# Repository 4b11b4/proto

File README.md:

# proto-pcb
free prototyping boards

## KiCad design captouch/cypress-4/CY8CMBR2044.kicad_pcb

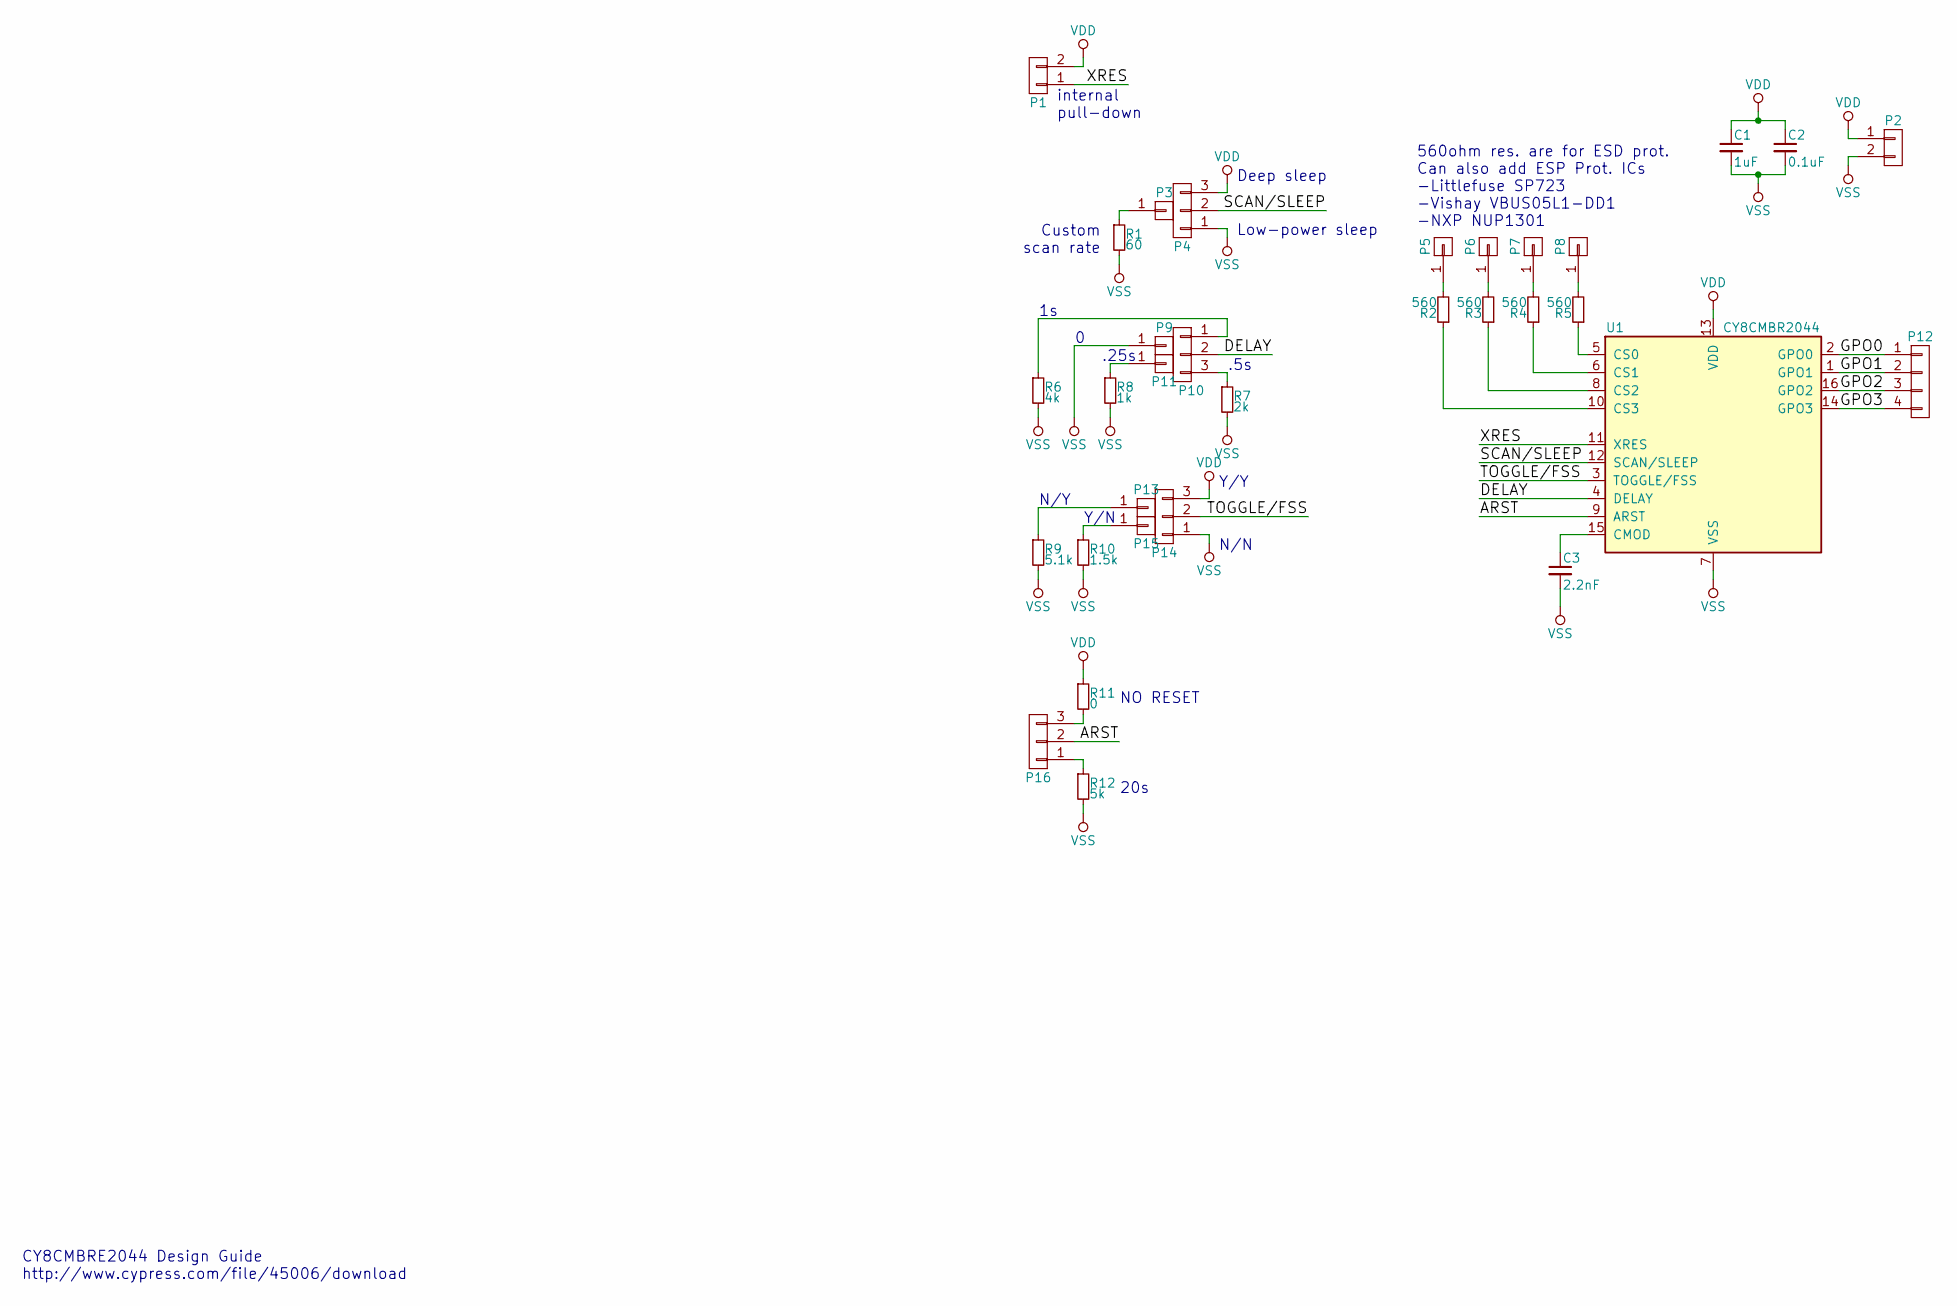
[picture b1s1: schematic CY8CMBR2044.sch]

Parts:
C1: 1uF; C_1206_HandSoldering
C2: 0.1uF; C_1206_HandSoldering
C3: 2.2nF; C_0603_HandSoldering; Mfr Part # GRM1885C1H222JA01D
P1, P2: CONN_01X02; Pin_Header_Straight_1x02
P3, P5, P6, P7, P8, P9, P11, P13, P15: CONN_01X01; Pin_Header_Straight_1x01
P4, P10, P14, P16: CONN_01X03; Pin_Header_Straight_1x03
P12: CONN_01X04; Pin_Header_Straight_1x04
R1: 60; R_1206_HandSoldering
R2, R3, R4, R5: 560; R_1206_HandSoldering
R6: 4k; R_1206_HandSoldering
R7: 2k; R_1206_HandSoldering
R8: 1k; R_1206_HandSoldering
R9: 5.1k; R_1206_HandSoldering
R10: 1.5k; R_1206_HandSoldering
R11: 0; R_1206_HandSoldering
R12: 5k; R_1206_HandSoldering
U1: CY8CMBR2044; QFN-16_3x3mm_Pitch0.5mm; Mfr Part # CY8CMBR2044

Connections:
/ARST: P16.2, U1.9 (ARST)
/DELAY: P10.2, U1.4 (DELAY)
/GPO0: P12.1, U1.2 (GPO0)
/GPO1: P12.2, U1.1 (GPO1)
/GPO2: P12.3, U1.16 (GPO2)
/GPO3: P12.4, U1.14 (GPO3)
/SCAN/SLEEP: P4.2, U1.12 (SCAN/SLEEP)
/TOGGLE/FSS: P14.2, U1.3 (TOGGLE/FSS)
/XRES: P1.1, U1.11 (XRES)
unnamed: C3.1, U1.15 (CMOD)
unnamed: P3.1, R1.1
unnamed: P5.1, R2.2
unnamed: P6.1, R3.2
unnamed: P7.1, R4.2
unnamed: P8.1, R5.2
unnamed: P10.1, R6.1
unnamed: P10.3, R7.1
unnamed: P11.1, R8.1
unnamed: P13.1, R9.1
unnamed: P15.1, R10.1
unnamed: P16.1, R12.1
unnamed: P16.3, R11.2
unnamed: R2.1, U1.10 (CS3)
unnamed: R3.1, U1.8 (CS2)
unnamed: R4.1, U1.6 (CS1)
unnamed: R5.1, U1.5 (CS0)
VDD: C1.1, C2.1, P1.2, P2.1, P4.3, P14.3, R11.1, U1.13 (VDD)
VSS: C1.2, C2.2, C3.2, P2.2, P4.1, P9.1, P14.1, R1.2, R6.2, R7.2, R8.2, R9.2, R10.2, R12.2, U1.7 (VSS)

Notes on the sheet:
CY8CMBRE2044 Design Guide http://www.cypress.com/file/45006/download
Y/Y
N/N
N/Y
Y/N
.25s
560ohm res. are for ESD prot. Can also add ESP Prot. ICs -Littlefuse SP723 -Vishay VBUS05L1-DD1 -NXP NUP1301
Low-power sleep
Deep sleep
Custom scan rate
NO RESET
20s
.5s
internal pull-down

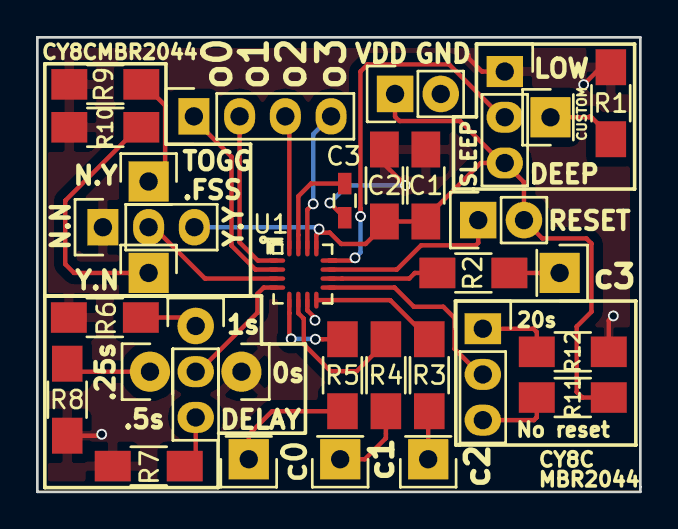
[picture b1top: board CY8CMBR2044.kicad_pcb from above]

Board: 2 copper layers, 33.5 x 25.2 mm, 32 parts (0 on the bottom side), 28 nets.

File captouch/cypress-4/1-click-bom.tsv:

References	Qty	Description	Digikey	Mouser	RS	Newark	Farnell
C1	1	1uF 0805 X5R					
C2	1	C Small 0.1uF Unpolarized capacitor 1206 HandSoldering					
C3	1	C Small 2.2nF Unpolarized capacitor 0603 HandSoldering					
P2, P1	2	CONN 01X02 Connector, single row, 01x02 Pin Header Straight 1x02					
P12	1	CONN 01X04 Connector, single row, 01x04 Pin Header Straight 1x04					
P13, P15, P9, P11, P3, P5, P6, P7, P8	9	CONN 01X01 Connector, single row, 01x01 Pin Header Straight 1x01					
P16, P14, P10, P4	4	CONN 01X03 Connector, single row, 01x03 Pin Header Straight 1x03					
R1	1	R Small 60 Resistor, small symbol 1206 HandSoldering					
R2, R3, R4, R5	4	R Small 560 Resistor, small symbol 1206 HandSoldering					
R6	1	R Small 4k Resistor, small symbol 1206 HandSoldering					
R7	1	R Small 2k Resistor, small symbol 1206 HandSoldering					
R8	1	R Small 1k Resistor, small symbol 1206 HandSoldering					
R9	1	R Small 5.1k Resistor, small symbol 1206 HandSoldering					
R10	1	R Small 1.5k Resistor, small symbol 1206 HandSoldering					
R11	1	R Small 0 Resistor, small symbol 1206 HandSoldering					
R12	1	R Small 5k Resistor, small symbol 1206 HandSoldering					
U1	1	CY8CMBR2044

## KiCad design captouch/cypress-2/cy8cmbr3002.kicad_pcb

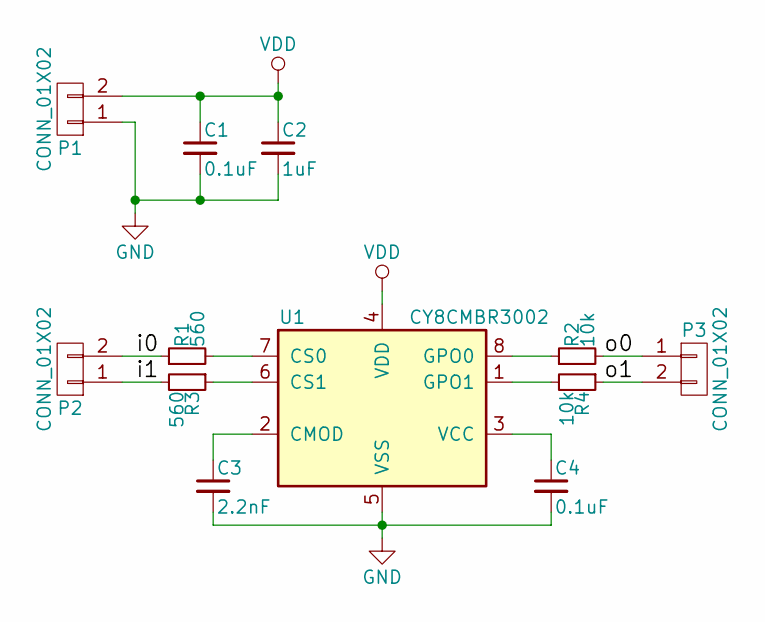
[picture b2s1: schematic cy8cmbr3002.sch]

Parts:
C1, C4: 0.1uF; C_1206_HandSoldering
C2: 1uF; C_1206_HandSoldering
C3: 2.2nF; C_1206_HandSoldering; Tolerance 5V X7R/NP0
P1, P2, P3: CONN_01X02; Pin_Header_Straight_1x02
R1, R3: 560; C_1206_HandSoldering
R2, R4: 10k; C_1206_HandSoldering
U1: CY8CMBR3002; SOIC-8-N; Mfr Part # CY8CMBR3002-SX1I

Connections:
/i0: P2.2, R1.1
/i1: P2.1, R3.2
/o0: P3.1, R2.2
/o1: P3.2, R4.1
GND: C1.2, C2.2, C3.2, C4.2, P1.1, U1.5 (VSS)
unnamed: C3.1, U1.2 (CMOD)
unnamed: C4.1, U1.3 (VCC)
unnamed: R1.2, U1.7 (CS0)
unnamed: R2.1, U1.8 (GPO0)
unnamed: R3.1, U1.6 (CS1)
unnamed: R4.2, U1.1 (GPO1)
VDD: C1.1, C2.1, P1.2, U1.4 (VDD)

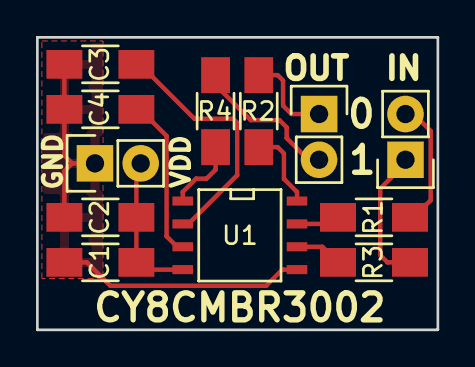
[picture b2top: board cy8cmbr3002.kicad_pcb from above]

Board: 2 copper layers, 22.3 x 16.2 mm, 12 parts (0 on the bottom side), 12 nets.

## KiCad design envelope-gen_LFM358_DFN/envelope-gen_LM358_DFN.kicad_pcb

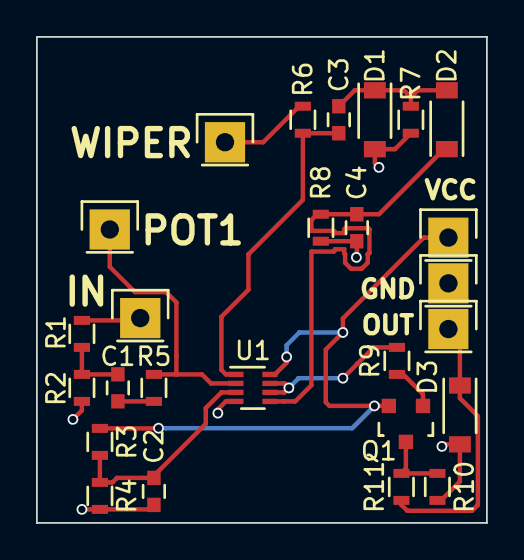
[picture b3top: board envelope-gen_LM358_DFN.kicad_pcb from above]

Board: 2 copper layers, 25.0 x 27.0 mm, 26 parts (0 on the bottom side), 15 nets.

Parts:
C1, C3: 0.22uF; C_0603
C2: 10uF; C_0603
C4: 1uF; C_0603
D1, D2: 1N4148; SOD-123
D3: 5.1V; SOD-123
P1, P2, P3, P4, P5, P6: CONN_01X01; Pin_Header_Straight_1x01
Q1: MMBT3904; SOT-23
R1, R2, R3, R4, R7, R10: 10k; R_0603
R5, R6, R9: 1k; R_0603
R8: 100k; R_0603
R11: 220; R_0603
U1: LM358; DFN-8_2x2mm_Pitch0.5mm

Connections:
/IN: P2.1, R1.1
/OUT: D3.1, P4.1, R11.2
/POT1: P5.1, R5.1, U1.2
/VCC: P3.1, Q1.2, R3.1, U1.8
/WIPER: P6.1, R6.2
GND: C2.2, C4.1, D1.2, D3.2, P1.1, R2.2, R4.2, R7.2, R8.2, R10.2, U1.4
unnamed: C1.1, R5.2
unnamed: C1.2, R1.2, R2.1
unnamed: C2.1, R3.2, R4.1, U1.3
unnamed: C3.1, D1.1, D2.2, R7.1
unnamed: C3.2, R6.1, U1.1
unnamed: C4.2, D2.1, R8.1, U1.5
unnamed: Q1.1, R9.1
unnamed: Q1.3, R10.1, R11.1
unnamed: R9.2, U1.6, U1.7

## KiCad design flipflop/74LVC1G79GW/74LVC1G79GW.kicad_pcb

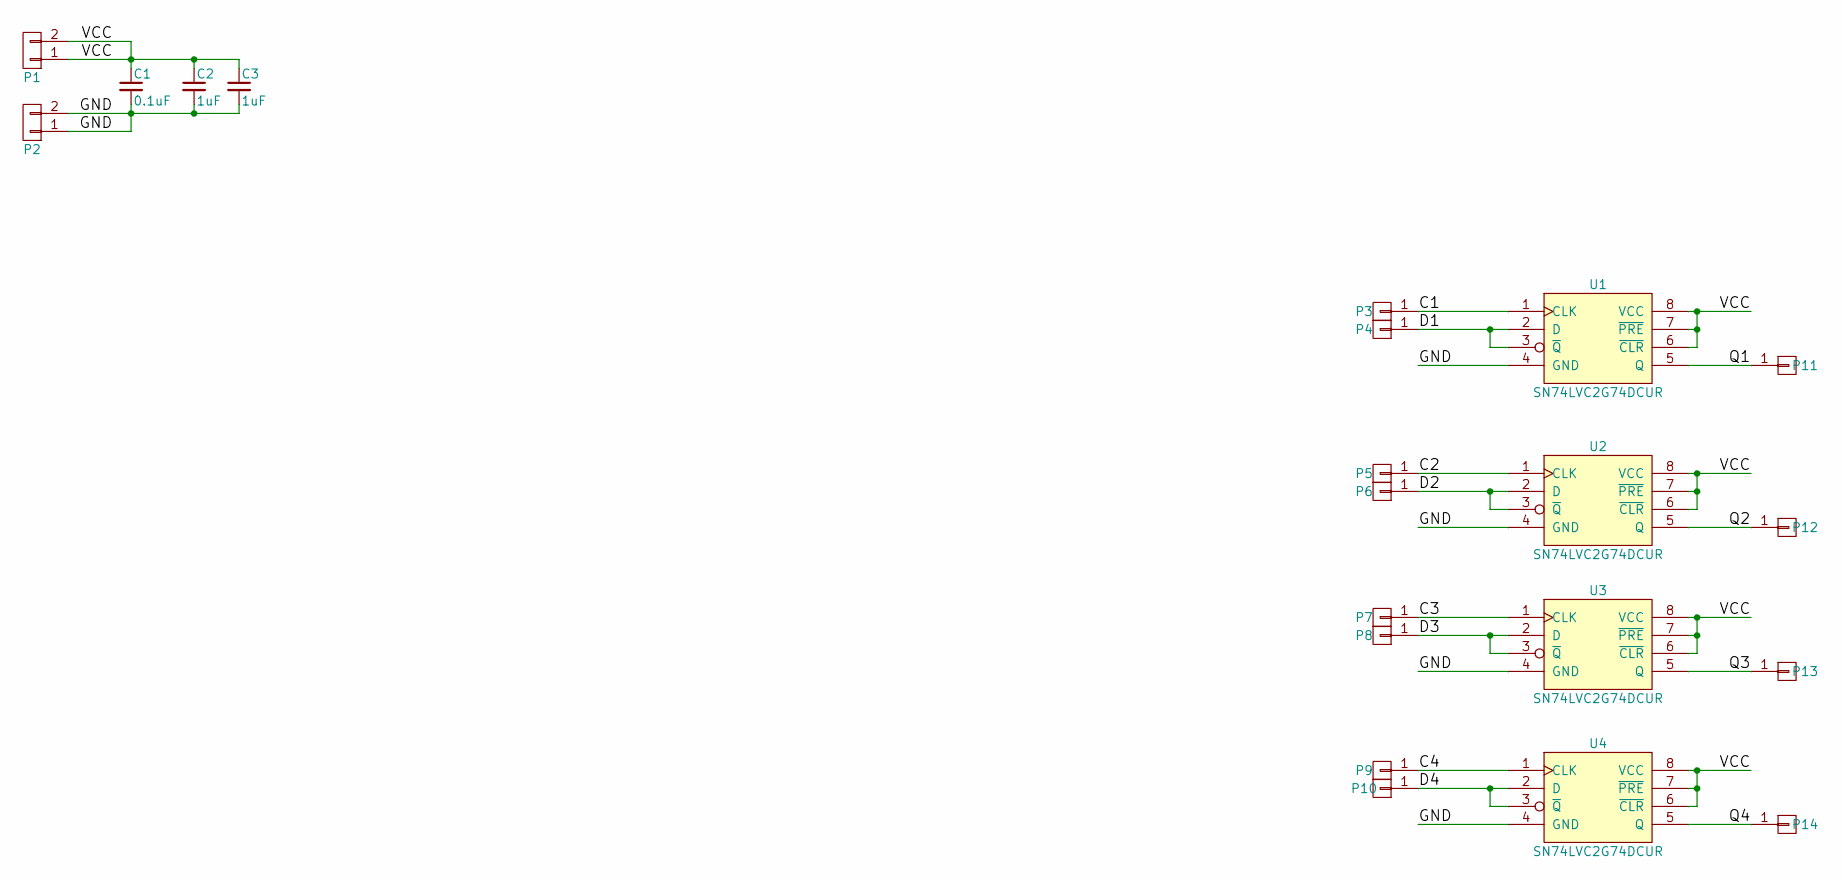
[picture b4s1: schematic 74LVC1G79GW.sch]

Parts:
C1: 0.1uF; C_0805
C2, C3: 1uF; C_0805
P1, P2: CONN_01X02; Pin_Header_Straight_1x02
P3, P4, P5, P6, P7, P8, P9, P10, P11, P12, P13, P14: CONN_01X01; Pin_Header_Straight_1x01
U1, U2, U3, U4: SN74LVC2G74DCUR; TSSOP-8_2x2.3mm_Pitch0.5mm; Mfr Part # SN74LVC2G74DCUR

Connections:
/C1: P3.1, U1.1 (CLK)
/C2: P5.1, U2.1 (CLK)
/C3: P7.1, U3.1 (CLK)
/C4: P9.1, U4.1 (CLK)
/D1: P4.1, U1.2 (D), U1.3 (~Q)
/D2: P6.1, U2.2 (D), U2.3 (~Q)
/D3: P8.1, U3.2 (D), U3.3 (~Q)
/D4: P10.1, U4.2 (D), U4.3 (~Q)
/GND: C1.2, C2.2, C3.2, P2.1, P2.2, U1.4 (GND), U2.4 (GND), U3.4 (GND), U4.4 (GND)
/Q1: P11.1, U1.5 (Q)
/Q2: P12.1, U2.5 (Q)
/Q3: P13.1, U3.5 (Q)
/Q4: P14.1, U4.5 (Q)
/VCC: C1.1, C2.1, C3.1, P1.1, P1.2, U1.6 (~CLR), U1.7 (~PRE), U1.8 (VCC), U2.6 (~CLR), U2.7 (~PRE), U2.8 (VCC), U3.6 (~CLR), U3.7 (~PRE), U3.8 (VCC), U4.6 (~CLR), U4.7 (~PRE), U4.8 (VCC)

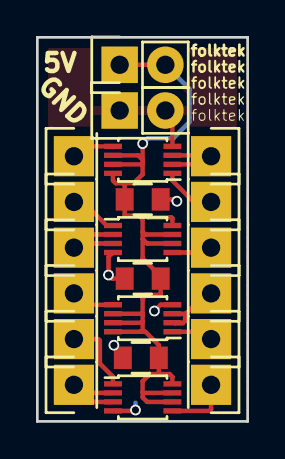
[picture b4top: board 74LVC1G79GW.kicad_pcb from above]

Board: 2 copper layers, 11.7 x 21.3 mm, 21 parts (0 on the bottom side), 14 nets.

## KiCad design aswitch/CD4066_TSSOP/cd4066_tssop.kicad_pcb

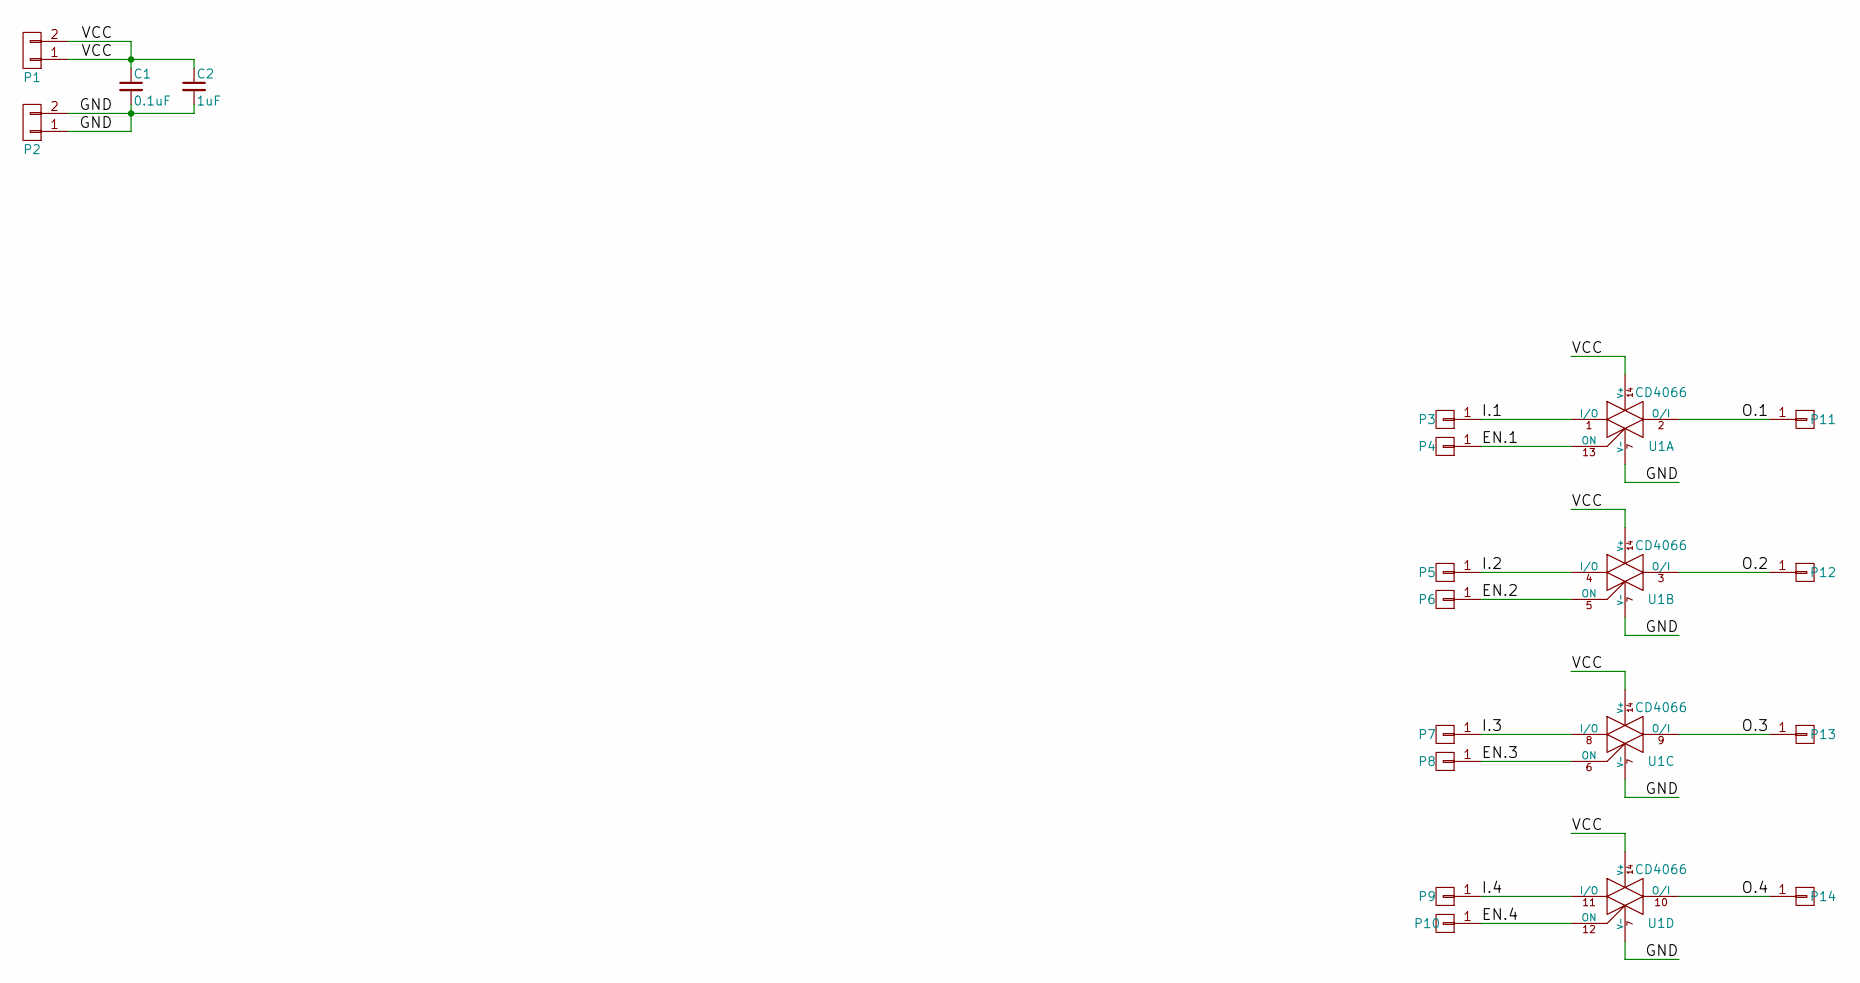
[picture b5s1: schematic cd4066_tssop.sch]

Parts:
C1: 0.1uF; C_0805
C2: 1uF; C_0805
P1, P2: CONN_01X02; Pin_Header_Straight_1x02
P3, P4, P5, P6, P7, P8, P9, P10, P11, P12, P13, P14: CONN_01X01; Pin_Header_Straight_1x01
U1: CD4066; TSSOP-14_4.4x5mm_Pitch0.65mm; Mfr Part # CD4066BPWR

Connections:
/EN.1: P4.1, U1.13 (ON)
/EN.2: P6.1, U1.5 (ON)
/EN.3: P8.1, U1.6 (ON)
/EN.4: P10.1, U1.12 (ON)
/GND: C1.2, C2.2, P2.1, P2.2, U1.7 (V-)
/I.1: P3.1, U1.1 (I/O)
/I.2: P5.1, U1.4 (I/O)
/I.3: P7.1, U1.8 (I/O)
/I.4: P9.1, U1.11 (I/O)
/O.1: P11.1, U1.2 (O/I)
/O.2: P12.1, U1.3 (O/I)
/O.3: P13.1, U1.9 (O/I)
/O.4: P14.1, U1.10 (O/I)
/VCC: C1.1, C2.1, P1.1, P1.2, U1.14 (V+)

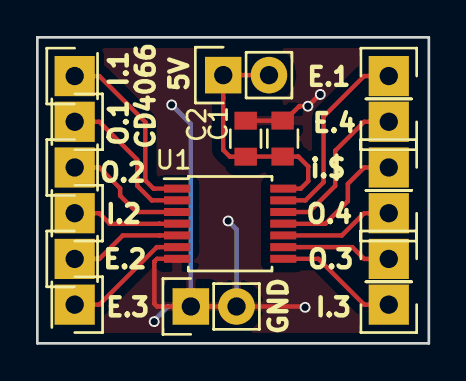
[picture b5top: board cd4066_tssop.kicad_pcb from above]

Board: 2 copper layers, 21.8 x 17.0 mm, 17 parts (0 on the bottom side), 14 nets.

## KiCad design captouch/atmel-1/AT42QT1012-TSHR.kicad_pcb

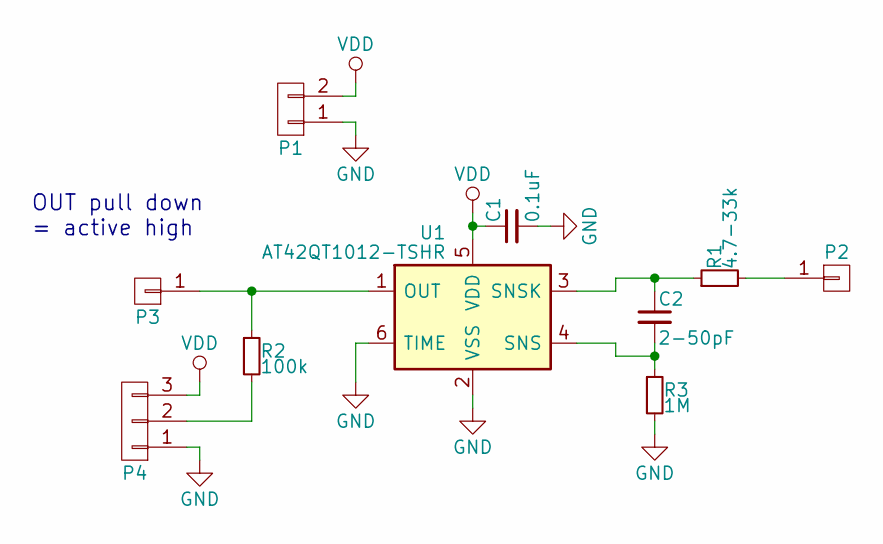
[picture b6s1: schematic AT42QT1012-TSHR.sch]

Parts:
C1: 0.1uF; C_1206_HandSoldering
C2: 2-50pF; C_1206_HandSoldering
P1: CONN_01X02; Pin_Header_Straight_1x02
P2, P3: CONN_01X01; Pin_Header_Straight_1x01
P4: CONN_01X03; Pin_Header_Straight_1x03
R1: 4.7-33k; R_1206_HandSoldering
R2: 100k; R_1206_HandSoldering
R3: 1M; R_1206_HandSoldering
U1: AT42QT1012-TSHR; SOT-23-6_Handsoldering; Mfr Part # AT42QT1012-TSHR

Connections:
GND: C1.2, P1.1, P4.1, R3.2, U1.2 (VSS), U1.6 (TIME)
unnamed: C2.1, R1.1, U1.3 (SNSK)
unnamed: C2.2, R3.1, U1.4 (SNS)
unnamed: P2.1, R1.2
unnamed: P3.1, R2.1, U1.1 (OUT)
unnamed: P4.2, R2.2
VDD: C1.1, P1.2, P4.3, U1.5 (VDD)

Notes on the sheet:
OUT pull down = active high

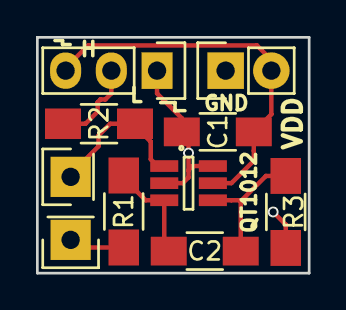
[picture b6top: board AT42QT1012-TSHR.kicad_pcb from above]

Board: 2 copper layers, 15.1 x 13.1 mm, 10 parts (0 on the bottom side), 7 nets.

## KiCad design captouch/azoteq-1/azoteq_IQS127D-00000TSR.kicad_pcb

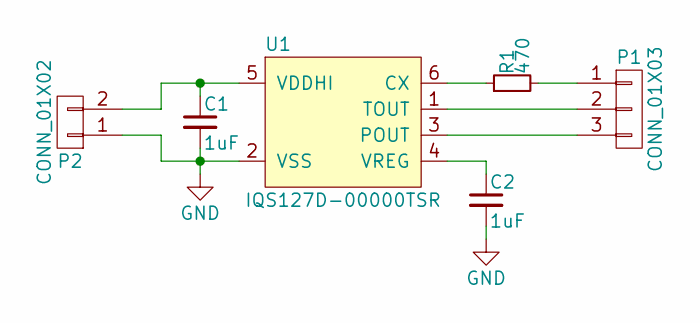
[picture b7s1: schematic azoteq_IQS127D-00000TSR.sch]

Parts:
C1, C2: 1uF; C_1206_HandSoldering
P1: CONN_01X03; Pin_Header_Straight_1x03
P2: CONN_01X02; Pin_Header_Straight_1x02
R1: 470; R_1206_HandSoldering
U1: IQS127D-00000TSR; SOT-23-6

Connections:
GND: C1.2, C2.2, P2.1, U1.2 (VSS)
unnamed: C1.1, P2.2, U1.5 (VDDHI)
unnamed: C2.1, U1.4 (VREG)
unnamed: P1.1, R1.2
unnamed: P1.2, U1.1 (TOUT)
unnamed: P1.3, U1.3 (POUT)
unnamed: R1.1, U1.6 (CX)

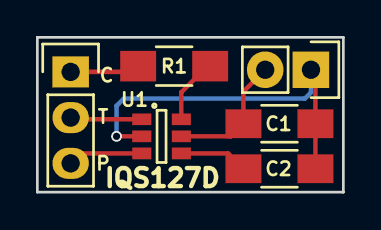
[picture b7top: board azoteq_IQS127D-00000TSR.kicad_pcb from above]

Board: 2 copper layers, 17.0 x 8.6 mm, 6 parts (0 on the bottom side), 7 nets.

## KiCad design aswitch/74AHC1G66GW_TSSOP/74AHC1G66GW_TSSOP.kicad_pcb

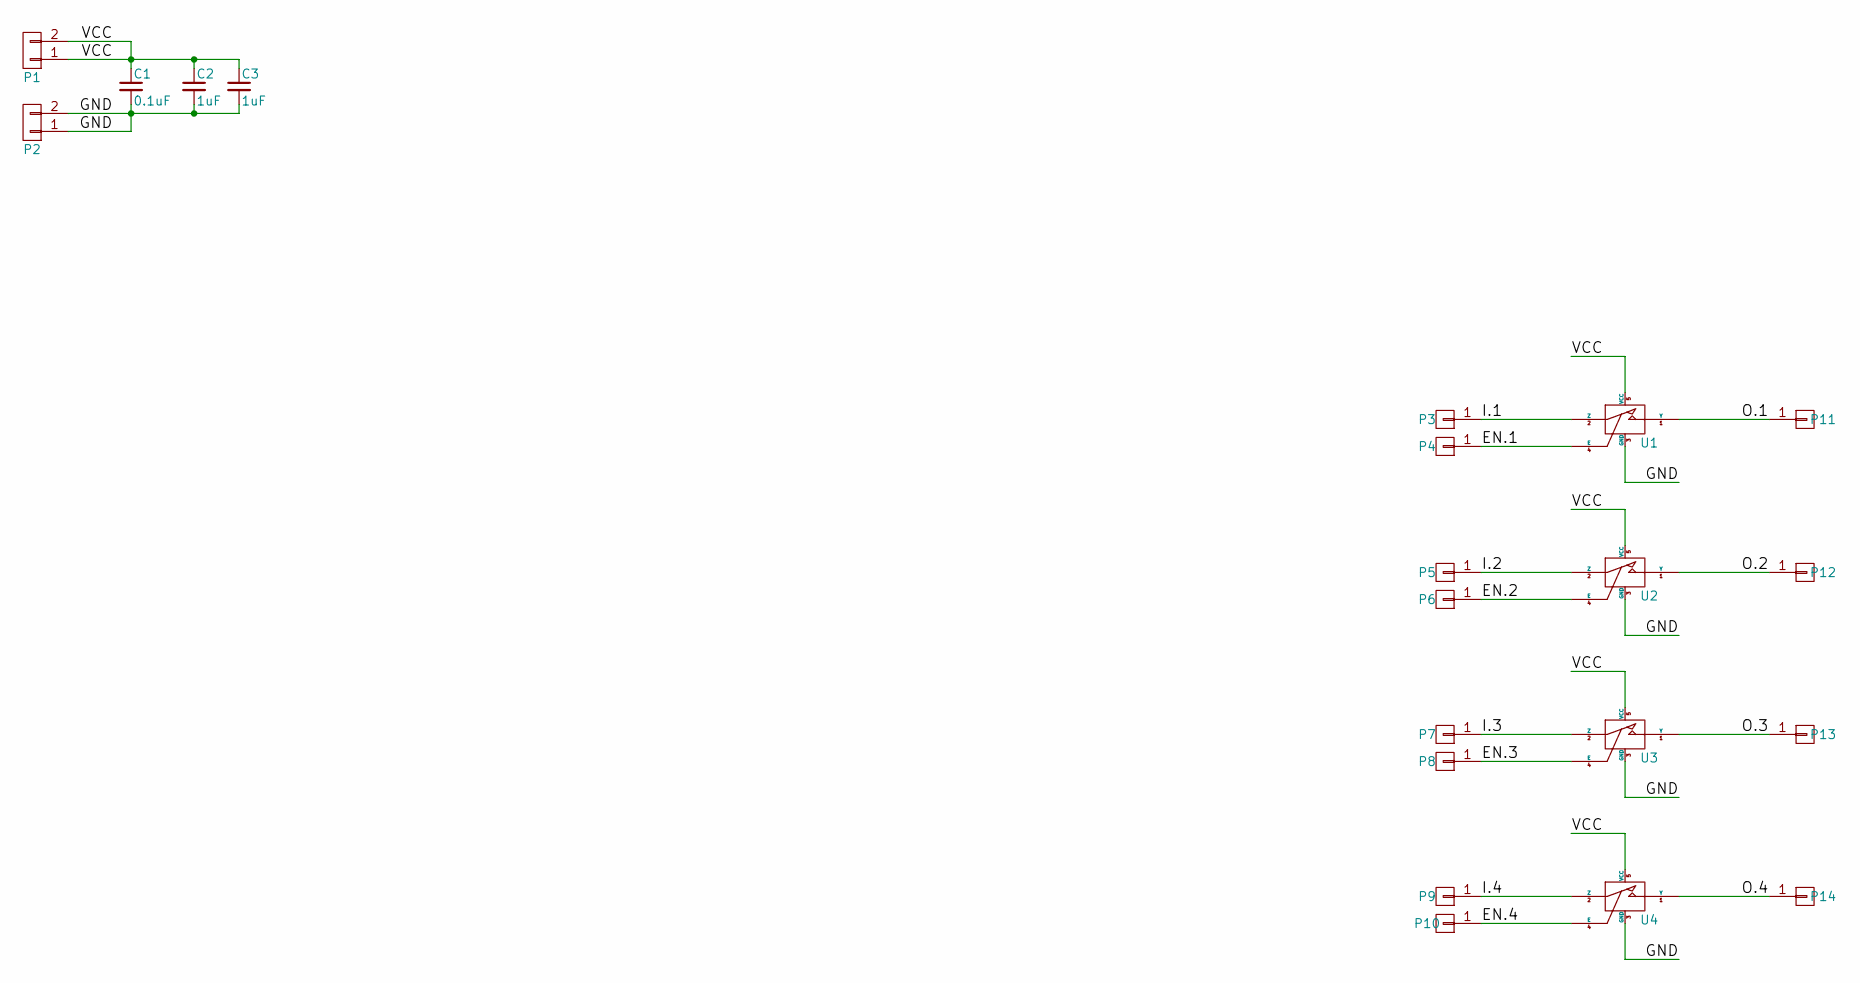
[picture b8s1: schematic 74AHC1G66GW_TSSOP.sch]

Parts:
C1: 0.1uF; C_0805
C2, C3: 1uF; C_0805
P1, P2: CONN_01X02; Pin_Header_Straight_1x02
P3, P4, P5, P6, P7, P8, P9, P10, P11, P12, P13, P14: CONN_01X01; Pin_Header_Straight_1x01
U1, U2, U3, U4: 74AHC1G66GW; TSSOP-5_1.25x2mm_Pitch0.65mm; Mfr Part # 74AHC1G66GW,125

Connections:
/EN.1: P4.1, U1.4 (E)
/EN.2: P6.1, U2.4 (E)
/EN.3: P8.1, U3.4 (E)
/EN.4: P10.1, U4.4 (E)
/GND: C1.2, C2.2, C3.2, P2.1, P2.2, U1.3 (GND), U2.3 (GND), U3.3 (GND), U4.3 (GND)
/I.1: P3.1, U1.2 (Z)
/I.2: P5.1, U2.2 (Z)
/I.3: P7.1, U3.2 (Z)
/I.4: P9.1, U4.2 (Z)
/O.1: P11.1, U1.1 (Y)
/O.2: P12.1, U2.1 (Y)
/O.3: P13.1, U3.1 (Y)
/O.4: P14.1, U4.1 (Y)
/VCC: C1.1, C2.1, C3.1, P1.1, P1.2, U1.5 (VCC), U2.5 (VCC), U3.5 (VCC), U4.5 (VCC)

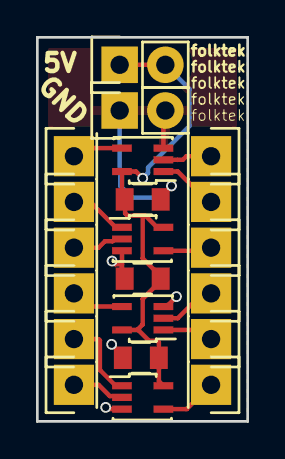
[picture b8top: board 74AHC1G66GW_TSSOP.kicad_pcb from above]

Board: 2 copper layers, 11.7 x 21.3 mm, 21 parts (0 on the bottom side), 14 nets.

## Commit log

2016-11-02 Add stuff
2016-11-03 Re-export gerbers at 0.1mm default line width, update .schs with KiField, wget wavegen ICL 8083
2016-11-08 Had not commited since I generated gerbers for p2_comp
2016-11-09 Good start on small dsp
2016-11-09 Trump is president
2016-12-03 Create BoM export from when Jean paul and I were protoyping
2016-12-03 Add piezo-preamp with kick
2016-12-03 Finalize TL072-piezo-amp schematic
